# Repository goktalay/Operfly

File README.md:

# OPERFLY

Operfly (Operational Flight), bir uçuş için gereken tüm kartların ve yazılımın tek ekosistem olarak
tasarlandığı kapalı bir sistemdir: uçuş kartları, kartlar arası omurga (Operfly Bus), gömülü yazılım,
kiracılı (çok kurumlu) merkez ve yer istasyonu. Operfly bileşenleri yalnızca birbirleriyle çalışır.

> **Bu depo özeldir (private).** Sır, özel anahtar, parola, canlı veritabanı dökümü veya müşteri verisi
> depoya eklenmez. Üretim çıktıları (gerber, kurulum paketleri) depoda değil, Releases altındadır.

## Ürünler

| Kod | Ad | İşlev | Kaynak |
|---|---|---|---|
| **OPFCOR** | Operfly Core | Uçuş kontrol kartı | `01_DONANIM/CORE/` |
| **OPFPWR** | Operfly Power | Batarya girişi, kart beslemeleri, akım/gerilim ölçümü | `01_DONANIM/POWER/` |
| **OPFVIS** | Operfly Vision | Görüntü işleme kartı (Jetson taşıyıcı, yalnızca Ethernet kamera) | `01_DONANIM/VISION/` |
| **OPFRAD** | Operfly Radio | Geniş bant radyo kartı: video + telemetri (2,4 GHz, 12 km, şifreli, mesh) | `01_DONANIM/RADIO/` |
| **OPFNAV** | Operfly Nav | GNSS kartı (RTK, karıştırma/aldatma tespiti) | `01_DONANIM/NAV/` |
| **OPFTRK** | Operfly Tracker | Anten takip birimi (yer tarafındaki yönlü anteni araca çevirir) | `01_DONANIM/TRACKER/` |
| **OPFSHD** | Operfly Shield | Karıştırma önleyici GNSS anteni: hazır 4 kanallı L1 CRPA modülü + arayüz kartı | `01_DONANIM/SHIELD/` |
| **OPFAIR** | Operfly Air | Hava hızı kartı (pitot fark basınç); sabit kanat için | `01_DONANIM/AIR/` |
| **OPFENG** | Operfly Engine | Benzinli motor izleme ve ateşleme kesme | `01_DONANIM/ENGINE/` |
| **OPFHUB** | Operfly Hub | Omurga anahtar kartı: tüm kartlar buna bağlanır (Gigabit anahtar, CAN FD, güç dağıtımı) | `01_DONANIM/HUB/` |
| **OPFBAS** | Operfly Base | RTK baz istasyonu (yer) | `01_DONANIM/BASE/` |
| **OPFGRD** | Operfly Ground Radio | Yer radyosu | `01_DONANIM/YER_RADYO/` |
| **OPFPCA** | Operfly PC adaptörü | Operfly Bus konnektörü ↔ USB Type-C aktif adaptör | `01_DONANIM/PC_ADAPTOR/` |
| **OPFCEL** | Operfly Cell | 5G kartı: telemetri ve görüntü için hücresel bağlantı | `01_DONANIM/CELL/` |
| **OPFR10 / OPFR30 / OPFR1H** | Operfly Range 10 / 30 / 100 | Mesafe sensörleri: 10 m, 30 m, 100 m | `01_DONANIM/RANGE_10/`, `RANGE_30/`, `RANGE_100/` |
| **OPFRCV** | Operfly RX | Araç tarafı kumanda alıcısı (12 kanal) | `01_DONANIM/RX/` |
| **OPFK12** | Operfly Pilot 12 | Kumanda: yalnızca 12 kanal | `01_DONANIM/KUMANDA_12/` |
| **OPFKTL** | Operfly Pilot T | Kumanda: 12 kanal + telemetri | `01_DONANIM/KUMANDA_T/` |
| **OPFKPR** | Operfly Pilot Pro | Kumanda: 10 inç ekran, yer istasyonu ve video (Jetson) | `01_DONANIM/KUMANDA_PRO/` |
| — | Ortak kart | Kumanda giriş kartı | `01_DONANIM/KUMANDA_GIRIS/` |
| **OPFKMD** | Kumanda yazılımı | Kumandalardaki gömülü yazılım | `02_GOMULU/KUMANDA/` |
| **OPFFLT** | Uçuş yazılımı | Operfly Core üzerinde çalışan otopilot | `02_GOMULU/UCUS/` |
| **OPFNOD** | Düğüm yazılımı | Çevre kartlarındaki Operfly Bus düğümü | `02_GOMULU/DUGUM/` |
| **OPFSEC** | Radyo/kripto yazılımı | Uçtan uca şifreleme, anahtar yönetimi, radyo modülü ayarları | `02_GOMULU/RADYO/` |
| **OPFMRK** | Merkez | Kiracılı çevrimiçi merkez: kurum, filo, cihaz, lisans, güncelleme | `03_MERKEZ/` |
| **OPFGCS** | Yer istasyonu | Çok araçlı görev, izleme ve sürü kontrolü | `04_YER_ISTASYONU/` |
| **OPFIMG** | Görüntü yazılımı | Operfly Vision üzerinde çalışan görüntü işleme | `05_GORUNTU/` |
| **OPFCMP / OPFADM / OPFWEB** | Paneller | Kurum paneli, yönetim paneli, tanıtım sitesi | `06_PANELLER/` |

Bu ürün kodları dosya, klasör, sürüm notu ve teknik iletişimde değişmeden kullanılır.

## Kapsam dışı (dışarıdan alınır)

Batarya, şarj cihazı, motor ve ESC şimdilik dışarıdan satın alınır. Sistem 2S–12S arasındaki hazır
bataryalarla çalışır; kendi bataryası ve şarj cihazı ertelenmiştir.

## Değişmez kurallar

1. **Kapalı ekosistem.** Operfly kartları ve yazılımı yalnızca kimliği doğrulanmış Operfly bileşenleriyle
   konuşur. Üçüncü taraf yer istasyonu yazılımları bağlanamaz.
2. **Marka temizliği.** Üçüncü taraf otopilot, protokol ve yer istasyonu adları kaynak adlarında, arayüzde,
   derlenmiş çıktıda ve cihazın dışarı verdiği hiçbir metinde geçmez. Bu adlar yalnızca
   `13_DOKUMANTASYON/` altında ve üçüncü taraf kaynak dosyalarının korunması zorunlu lisans başlıklarında
   bulunur. Denetim: `10_ORTAK_ARACLAR/marka_denetle.py`.
3. **Kiracı yalıtımı.** Her kurumun cihazları, anahtarları ve verisi diğer kurumlardan ayrıdır.
4. **Sürü önceliği.** Her bileşen çok araçlı kullanım varsayılarak tasarlanır.

Ayrıntı: `13_DOKUMANTASYON/MIMARI.md`.

## Sahiplik

© 2026 Muhammed Kaderoğlu. Tüm hakları saklıdır. Bu depodaki tasarım dosyaları ve yazılım izinsiz
kopyalanamaz, dağıtılamaz veya kullanılamaz.

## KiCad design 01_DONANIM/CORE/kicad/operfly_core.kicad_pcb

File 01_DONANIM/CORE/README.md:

## Pin haritası (15 Kasım 2026)

- Atamalar: `pin_atamalari.csv` (kaynak dosya). Okunabilir tablo: `PIN_HARITASI.md` (üretilir).
- Doğrulama: `python 10_ORTAK_ARACLAR/kicad/pin_cikar.py <KiCad>/symbols/MCU_ST_STM32H7.kicad_sym STM32H753IIKx out/h753iik.json`
  ardından `python 10_ORTAK_ARACLAR/kicad/pin_dogrula.py out/h753iik.json 01_DONANIM/CORE/pin_atamalari.csv 01_DONANIM/CORE/PIN_HARITASI.md "<başlık>"`.
- Kılıf: UFBGA 176+25, 10 x 10 mm, 0,65 mm adım.

Pin haritasından çıkan tasarım notları:

- İşlemcinin Ethernet arayüzü en çok 100 Mbit destekler (MII/RMII). Core–Hub bağlantısı 100 Mbit olur; PTP zaman damgası korunur.
  Core'daki PHY buna göre 10/100 RMII tipinde seçilecek. Omurganın geri kalanı gigabit kalır.
- Uçuş kaydı için microSD yuvası önerildi (SDMMC1 pinleri ayrıldı); onay bekliyor.
- Üç IMU ayrı SPI hatlarında ve ayrı besleme anahtarlarındadır; bir sensörün arızası diğerlerini etkilemez.
- 12 çıkış üç ayrı zamanlayıcıdadır (4 + 4 + 4); DShot ve PWM grupları buna göre seçilir.

## Mimari kararlar (15 Kasım 2026)

- **Çıkışlar:** 12 çıkışın ilk 8'i IO/failsafe işlemcisinin denetimindedir, son 4'ü doğrudan ana işlemciden çıkar.
  İlk 8 çıkışta ana işlemcinin zamanlayıcı sinyali ile IO işlemcisinin sinyali arasında seçim yapan bir anahtar bulunur;
  seçimi IO işlemcisi yapar. Ana işlemci çalışırken DShot dahil tüm protokoller ondan geçer; ana işlemci durursa
  IO işlemcisi çıkışları devralır ve güvenli değerleri sürer.
- **IO/failsafe işlemcisi omurgaya doğrudan bağlıdır (CAN B).** Kumanda alıcısı (RX) omurgada olduğu için IO işlemcisi,
  ana işlemci durduğunda kumandayı ancak CAN üzerinden alabilir. Bu yüzden CAN FD destekli bir işlemci gerekir;
  öneri düğüm işlemcisiyle aynı aile (STM32G0B1). Önceki STM32F103 önerisi CAN FD desteklemediği için bırakıldı.
- **İkinci Bus portu** yalnızca yedek güç ve CAN taşır; Ethernet ve PPS bağlı değildir.
- Sınır: DShot ile sürülen motorlarda IO işlemcisinin devralması motoru güvenli değere getiremez (ESC protokolü açılışta
  seçilir); bu çıkışlarda failsafe, sinyalin kesilmesiyle ESC'nin kendi davranışına dayanır. Servolar ve PWM ESC'lerde
  devralma tam çalışır.

## KiCad projesi (15 Kasım 2026)

- Proje: `kicad/operfly_core.kicad_pro`. Şematik `kicad/uret.py` ile üretilir; `*.kicad_sch` dosyaları ve kütüphane
  tabloları elle düzenlenmez.
- Üretim ve denetim tek komut: `python 10_ORTAK_ARACLAR/kicad/denetle.py CORE operfly_core` (üretir, güncel biçime çevirir,
  ERC çalıştırır, `out/core.pdf` çıkarır).
- Sayfalar: kök (`operfly_core`), omurga portları (`omurga`), işlemci (`islemci`), güç (`guc`), saat/sıfırlama/ayırma
  kondansatörleri (`islemci_destek`), Ethernet/CAN/USB/microSD/PPS (`haberlesme`), sensörler/bellek/güvenli eleman
  (`sensorler`), IO işlemcisi ve çıkışlar (`io`), gözetim/enerji deposu/Peltier (`gozetim`).
- Durum: şematik tamam; ERC 0 hata, 0 uyarı. Sıradaki iş doğrulama listesi ve kart çizimi.
- Diğer kartlar ortak yardımcıları kullanır: `10_ORTAK_ARACLAR/kicad/kart.py` ve `dugum.py` (düğüm devresi).

## Güç ve işlemci destek kararları (15 Kasım 2026, sahibinin onayı beklenmeden alındı)

Bu kararlar gece çalışmasında, onay sorulmadan alındı. Her biri tek satırla geri alınabilir; değiştirilmesi istenen olursa
`kicad/uret.py` içinde ilgili satır düzeltilip şematik yeniden üretilir.

1. **İki omurga girişi diyotla birleştirilir** (2 x Schottky, 60 V 3 A). Basit ve arıza toleranslı; karşılığı diyot
   başına yaklaşık 0,4 V kayıp. İdeal diyot denetleyicisi (kayıpsız) sonraki revizyon için açık seçenek.
2. **Aşırı gerilim koruması:** girişte 18 V kırpma diyotu (SMBJ18A). Omurga 12 V olduğu için 18 V seçildi.
3. **5 V ve 3,3 V ayrı ayrı 12 V'tan üretilir** (AP63205 ve AP63203, 2 A, sabit çıkışlı). Biri arızalanırsa diğeri
   etkilenmez. Otomotiv sınıfı (Q) sürümleri -40..+125 °C çalışır; standart sürüm +85 °C ile sınırlıdır, bu yüzden
   malzeme listesine Q sürümü yazıldı.
4. **Her IMU'nun kendi 3,3 V regülatörü var** (LP5907, düşük gürültü), işlemci tek tek açıp kapatabilir (SENS1/2/3_EN).
   Varsayılan kapalıdır (aşağı çekme direnci); takılan bir sensör güç kesilerek sıfırlanabilir.
5. **Analog besleme** ferrit üzerinden süzülür; ADC referansı ayrıca 10 ohm + kondansatörle süzülür. Ayrı referans
   entegresi yok (ölçümler besleme izleme amaçlı, yüksek doğruluk gerekmiyor).
6. **Yedek pil yok:** VBAT 3,3 V'a bağlı. Saat bilgisi GNSS ve ağ zaman eşlemesinden gelir.
7. **Kristaller:** ana saat 16 MHz, gerçek zaman saati 32,768 kHz. Yük kondansatörü değerleri kristal parça numarası
   seçilince doğrulanacak.
8. **Açılış:** BOOT0 aşağı çekili (her zaman uygulamadan açılır). Fabrika yüklemesi SWD üzerinden yapılır.
9. **Besleme ölçümleri:** 12 V 11:1, 5 V ve 1. sensör beslemesi 2:1 bölücüyle işlemciye gider (36 V'a kadar güvenli).

Doğrulanacaklar (kart çizimine geçmeden): bobin parça numaraları ve doyma akımları, giriş diyotlarında ısıl hesap,
5 V hattının toplam akımı (IO işlemcisi, sensör regülatörleri, omurga dışı yükler), kristal yük kondansatörleri.

## Haberleşme kararları (15 Kasım 2026, sahibinin onayı beklenmeden alındı)

1. **Ethernet alıcı-vericisi LAN8742A**, 50 MHz osilatörle. Aynı saat hem alıcı-vericiye hem işlemciye gider; zaman
   eşlemesi (PTP) için en temiz düzen budur. Karşılığı: kristal yerine osilatör (biraz daha pahalı).
2. **Ethernet hattında trafo var** (Bourns PT61017PEL). Kartlar arası kabloda standart ve en güvenli yol; kartlar arasında
   toprak döngüsünü keser. Trafosuz (kondansatörlü) bağlantı yer kazandırır ama Hub tarafıyla birlikte kararlaştırılmalı.
3. **CAN alıcı-vericisi TJA1051-3** (CAN FD, 5 Mbit/s), her hatta ayrı. İşlemci pinindeki `CAN_x_STB` sinyali bu parçada
   "sessiz mod" girişidir (bekleme değil): yüksekken kart hattı yalnızca dinler.
4. **CAN sonlandırma dirençleri Core'da dizilmez**, yerleri hazırdır. Sonlandırma Hub'dadır.
5. **USB kartı beslemez.** Servis portu yalnızca veri taşır; kart her zaman omurgadan (12 V) beslenir. USB ile masa
   üstünde beslemek istenirse 5 V hattına güç seçici eklenmesi ve 3,3 V regülatörünün 5 V'tan beslenmesi gerekir
   (açık seçenek; ek parça ve kart alanı ister).
6. **microSD beslemesi anahtarlanmaz**, doğrudan 3,3 V'a bağlıdır. Kart kilitlenirse yeniden başlatma gerekir.
7. **PPS 3,3 V lojik** olarak tanımlandı ve omurga belgesine yazıldı. Core girişi 5 V'a dayanıklıdır.
8. `ETH_PPS_OUT` (işlemcinin ürettiği saniye darbesi) şimdilik yalnızca ölçüm noktasına çıkar.

Doğrulanacaklar: trafo pin sırası ve ayak izi (üretici belgesiyle), Hub tarafının 100 Mbit bağlantıda A/B çiftlerini
kullandığı, CAN hattında kabul edilen en yüksek hız için kablo boyu.

## Sensör ve IO işlemcisi kararları (15 Kasım 2026, sahibinin onayı beklenmeden alındı)

1. **Sensör beslemeleri:** 1. hat IMU 1 + barometre 1 + pusula, 2. hat IMU 2 + barometre 2, 3. hat IMU 3. Bir hat
   kapatıldığında o hattaki sensörlerin bağlı olduğu I2C hattı da kullanılamaz (yalnızca sıfırlama sırasında kapatılır).
2. **Barometre 2: MS5611-01BA03** (ICP-20100 yerine). Dağıtıcı ICP-20100'ü "yeni tasarımlar için önerilmez" olarak
   listeliyor. MS5611 farklı üretici ve farklı ölçüm ilkesi; barometre 1 (BMP390) ile ortak hata riskini azaltır.
3. **Güvenli eleman SE050:** `SE_NRST` hattı elemanın güç anahtarı girişini (ENA) sürer. I2C kullanımında ayrı bir
   sıfırlama girişi olmadığı için sıfırlama, beslemesini kesip vererek yapılır.
4. **FRAM: FM25V10** (1 Mbit, SOIC-8).
5. **IO/failsafe işlemcisi: STM32G0B1CET6** (LQFP-48). Kendi 3,3 V regülatörü, kendi kristali ve CAN B üzerinde kendi
   alıcı-vericisi vardır. Pin atamaları `io_pin_atamalari.csv` içindedir ve KiCad pin verisiyle denetlenmiştir.
6. **Çıkış seçici: 2 x TMUX1574** (analog anahtar). Sayısal seçici yerine analog anahtar seçildi çünkü iki yönlü motor
   protokollerini (telemetrili DShot) geçirir. Seçme girişi aşağı çekilidir: IO işlemcisi çalışmıyorken 1-8. çıkışları ana
   işlemci sürer; IO işlemcisi devralmak istediğinde girişi yükseltir. Anahtarlar 5 V'tan beslenir (iki 3,3 V hattından
   bağımsız).
7. **Çıkış konnektörü (26 kontak):** tek numaralı kontaklar 1-12. çıkış, çift numaralı kontaklar GND, 25. kontak boş.
   Her çıkışta 33 ohm seri direnç var. Çıkışlarda ayrıca ESD koruması yok (sonraki revizyon için açık).
8. **IO işlemcisi yazılım yükleme:** ana işlemci `IO_NRST` ile sıfırlar ve seri hattan yükler. `IO_BOOT0`, IO işlemcisinin
   BOOT0/SWCLK ortak pinine 10 k ile bağlıdır; hata ayıklayıcı takılıyken hata ayıklayıcı baskın gelir.
9. **Durum LED'leri** sıfırda yanar. Kart sürümü dirençleri A revizyonu için yerleştirildi (sürüm 1:1, revizyon 10:1).
10. **Hata ayıklama:** ana işlemci için 2x5 (1,27 mm) SWD konnektörü; konsol ve IO işlemcisi SWD hatları ölçüm noktasında.

### Doğrulanacaklar (kart çizimine geçmeden)

- BMP390 ve SE050 ayak izleri geçici; üretici çizimiyle yapılacak. IMU ayak izlerinde pin sırası bir kez daha bakılacak.
- IST8310 VPP ucu boş bırakıldı; üretici belgesindeki öneriyle karşılaştırılacak.
- ICM-42688-P ayrılmış uçları: 7 ve 11 GND'ye, 2, 3 ve 10 boş.
- TMUX1574: seçme girişinin yönü (0 = A kolu) ve 5 V beslemede 3,3 V lojikle sürülmesi.
- STM32G0B1 fabrika yükleyicisinin PA2/PA3 seri hattını desteklediği (boş işlemcinin ana işlemci üzerinden yüklenmesi).
- TPS3808G01 eşik gerilimi (0,405 V varsayıldı) ve 470 µF 25 V kondansatörün 8x10 mm kılıfta bulunabilirliği.
- Enerji deposunun ilk şarj akımı: Hub port anahtarı yaklaşık 1000 µF yükü açılışta kaldırmalı.

## Gözetim ve Peltier kararları (15 Kasım 2026; sahibi kararı tasarımcıya bıraktı)

1. **Harici watchdog ana işlemciyi sıfırlamaz, IO işlemcisini uyarır.** Ana işlemci darbe göndermeyi keserse
   `FMU_FAULT_N` 200 ms sıfıra iner; IO işlemcisi 1-8. çıkışları devralır ve güvenli değerleri sürer. Gerekçe: uçuşta
   donanımın kendiliğinden sıfırlama yapması, yazılım güncelleme ve hata ayıklama sırasında da tetiklenir ve sıfırlama
   döngüsüne yol açabilir. Ana işlemci takılırsa kendi iç watchdog'u onu sıfırlar; o yeniden başlayana kadar uçağı IO
   işlemcisi tutar.
2. **Watchdog penceresi:** darbe aralığı 10-93 ms arasında olmalı (yazılım 30-50 ms'de bir gönderir); kesinti en geç
   yaklaşık 125 ms içinde algılanır. Watchdog IO işlemcisinin beslemesinden çalışır.
3. **IO işlemcisi ana işlemciyi sıfırlayabilsin diye bir hat ayrıldı** (`IO_FMU_RST`) ama direnci dizilmez. İleride
   istenirse tek direnç takılarak açılır.
4. **Güç kesintisi algılama:** giriş 10,1 V altına inince `PWR_FAIL_N` sıfıra iner; işlemci kritik durumu FRAM'e yazar.
5. **Enerji deposu: 2 x 470 µF.** Kesintiden sonra kartı yaklaşık 10-20 ms taşır (kart tüketimi 2-3 W varsayımıyla
   hesap; ölçülecek). FRAM yazımı için yeterlidir; microSD'deki son birkaç yüz milisaniyelik kayıt kaybolabilir.
   Süper kondansatörlü daha uzun taşıma, kart alanı ve şarj devresi gerektirdiği için seçilmedi.
6. **Peltier sürücüsü: DRV8837**, 5 V'tan, en çok 1 A. Çıkışta bobin ve kondansatör var (anahtarlama gürültüsü pusula
   ve IMU'yu bozmasın diye). Isıl hedef varsayılan 45 °C, yazılımla değişir; sıcaklık IMU'ların kendi sensöründen okunur.
   Peltier modülünün kendisi mekanik tasarımla birlikte seçilecek (en çok 5 V, 1 A).

## Kart çizimi (otomatik)

Sahibinin kararıyla kart **otomatik** çizildi: yerleşim `pcb_yerlesim.py`, yollar dış bir otomatik yol çiziciyle
(`pcb_ciz.py`). Dosya: `kicad/operfly_core.kicad_pcb`; ayarlar `kicad/pcb_ayar.py`.
Yeniden üretmek için: `python 10_ORTAK_ARACLAR/kicad/pcb_ciz.py CORE operfly_core`.

- **Kart:** 125 x 85 mm, 6 katman (iç 1: toprak, iç 4: +3V3; diğer katmanlar sinyal, elemanlar üstte), 264 eleman, tamamı üst yüzde; köşelerde M3 montaj deliği.
- **Kurallar:** yol 0,10 mm, açıklık 0,100 mm, geçiş 0,40/0,20 mm; besleme ağları, ağın en dar ucunu aşmayacak biçimde 0,2-1,0 mm (0,4 mm ve üstünde geçiş 0,8/0,4 mm); bakır-kenar 0,25 mm.
- **Denetim: KART TAMAMLANMADI.** DRC 0 ihlal (-), 3 bağlanmamış uç. Otomatik yol çizici bu kartı bitiremedi;
  kalan bağlantılar elle çizilmeli ya da yerleşim elle düzeltilip yeniden denenmeli.

**Bu bir mühendis çizimi değildir.** Üretimden önce bir kart tasarımcısının bakması gereken noktalar:

- Eksik kalan üç bağlantı: +3V3, +3V3_S2, IMU2_MOSI. Üç ayrı yerleşim denendi (ilki 120 turda 4 eksik, ikincisi 10 eksik, bu üçüncüsü 60 turda 3 eksik; `OPERFLY_YOL_CIZICI` 1.9.0, `OPERFLY_YOL_TUR=60`, deneme başına yaklaşık 3 saat). Otomatik yol çizici bu kartı bitiremiyor; kalanlar elle çizilmeli.
- İşlemci 0,65 mm adımlı BGA olduğu için ince kural kullanıldı (yol ve açıklık 0,10 mm, geçiş 0,4/0,2 mm): bu, standart değil ileri sınıf üretim ister; üreticinin yetenekleriyle karşılaştırılmalı.
- Üç IMU'nun mekanik yalıtımı, ısıtıcı/Peltier bölgesi ve IMU'ların ısı kaynaklarından uzaklığı gözetilmedi; uçuş denetçisinde ölçüm kalitesi doğrudan buna bağlıdır.
- İşlemci çekirdek beslemesi ve BGA altı ayırma kondansatörleri üretici önerisine göre yerleştirilmedi; Ethernet (RMII), USB ve microSD hatları eşit uzunlukta çizilmedi.
- Servo/motor çıkışları (12 kanal) ve yedek işlemci yolu için gürültü ve arıza yalıtımı gözetilmedi.
- Anahtarlamalı regülatörlerin (bobin, diyot, giriş/çıkış kondansatörleri) akım döngüleri küçük tutulmadı; gürültü ve verim ölçülmeli.
- Kristal ve osilatör hatları en kısa yoldan çizilmedi; altlarından başka sinyal geçip geçmediğine bakılmalı.
- Fark çiftleri (CAN, USB, Ethernet) çift olarak, eşit uzunlukta ve empedans denetimli çizilmedi.
- Güç elemanlarının soğutma bakırı ve ısıl geçişleri ayrıca hesaplanmadı.
- Eleman adları üretim katmanında bırakıldı; kart üstünde yazı (serigrafi) yok.
- Kasa, konnektör yerleri ve montaj delikleri mekanik tasarımla eşleştirilmedi.
- Üretim dosyaları (Gerber, delik, dizgi) henüz çıkarılmadı.

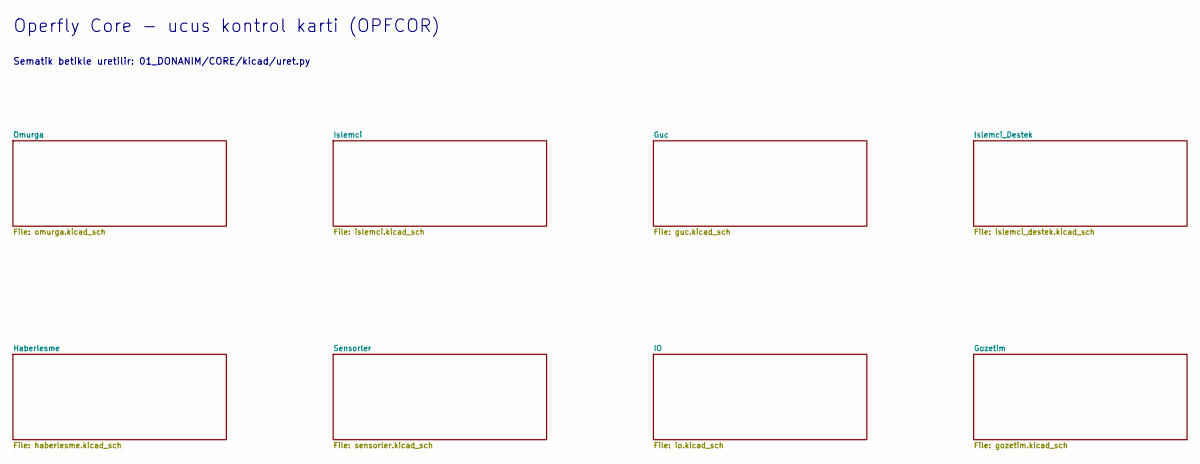
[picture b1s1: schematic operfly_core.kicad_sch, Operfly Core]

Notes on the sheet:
Operfly Core - ucus kontrol karti (OPFCOR)
Sematik betikle uretilir: 01_DONANIM/CORE/kicad/uret.py

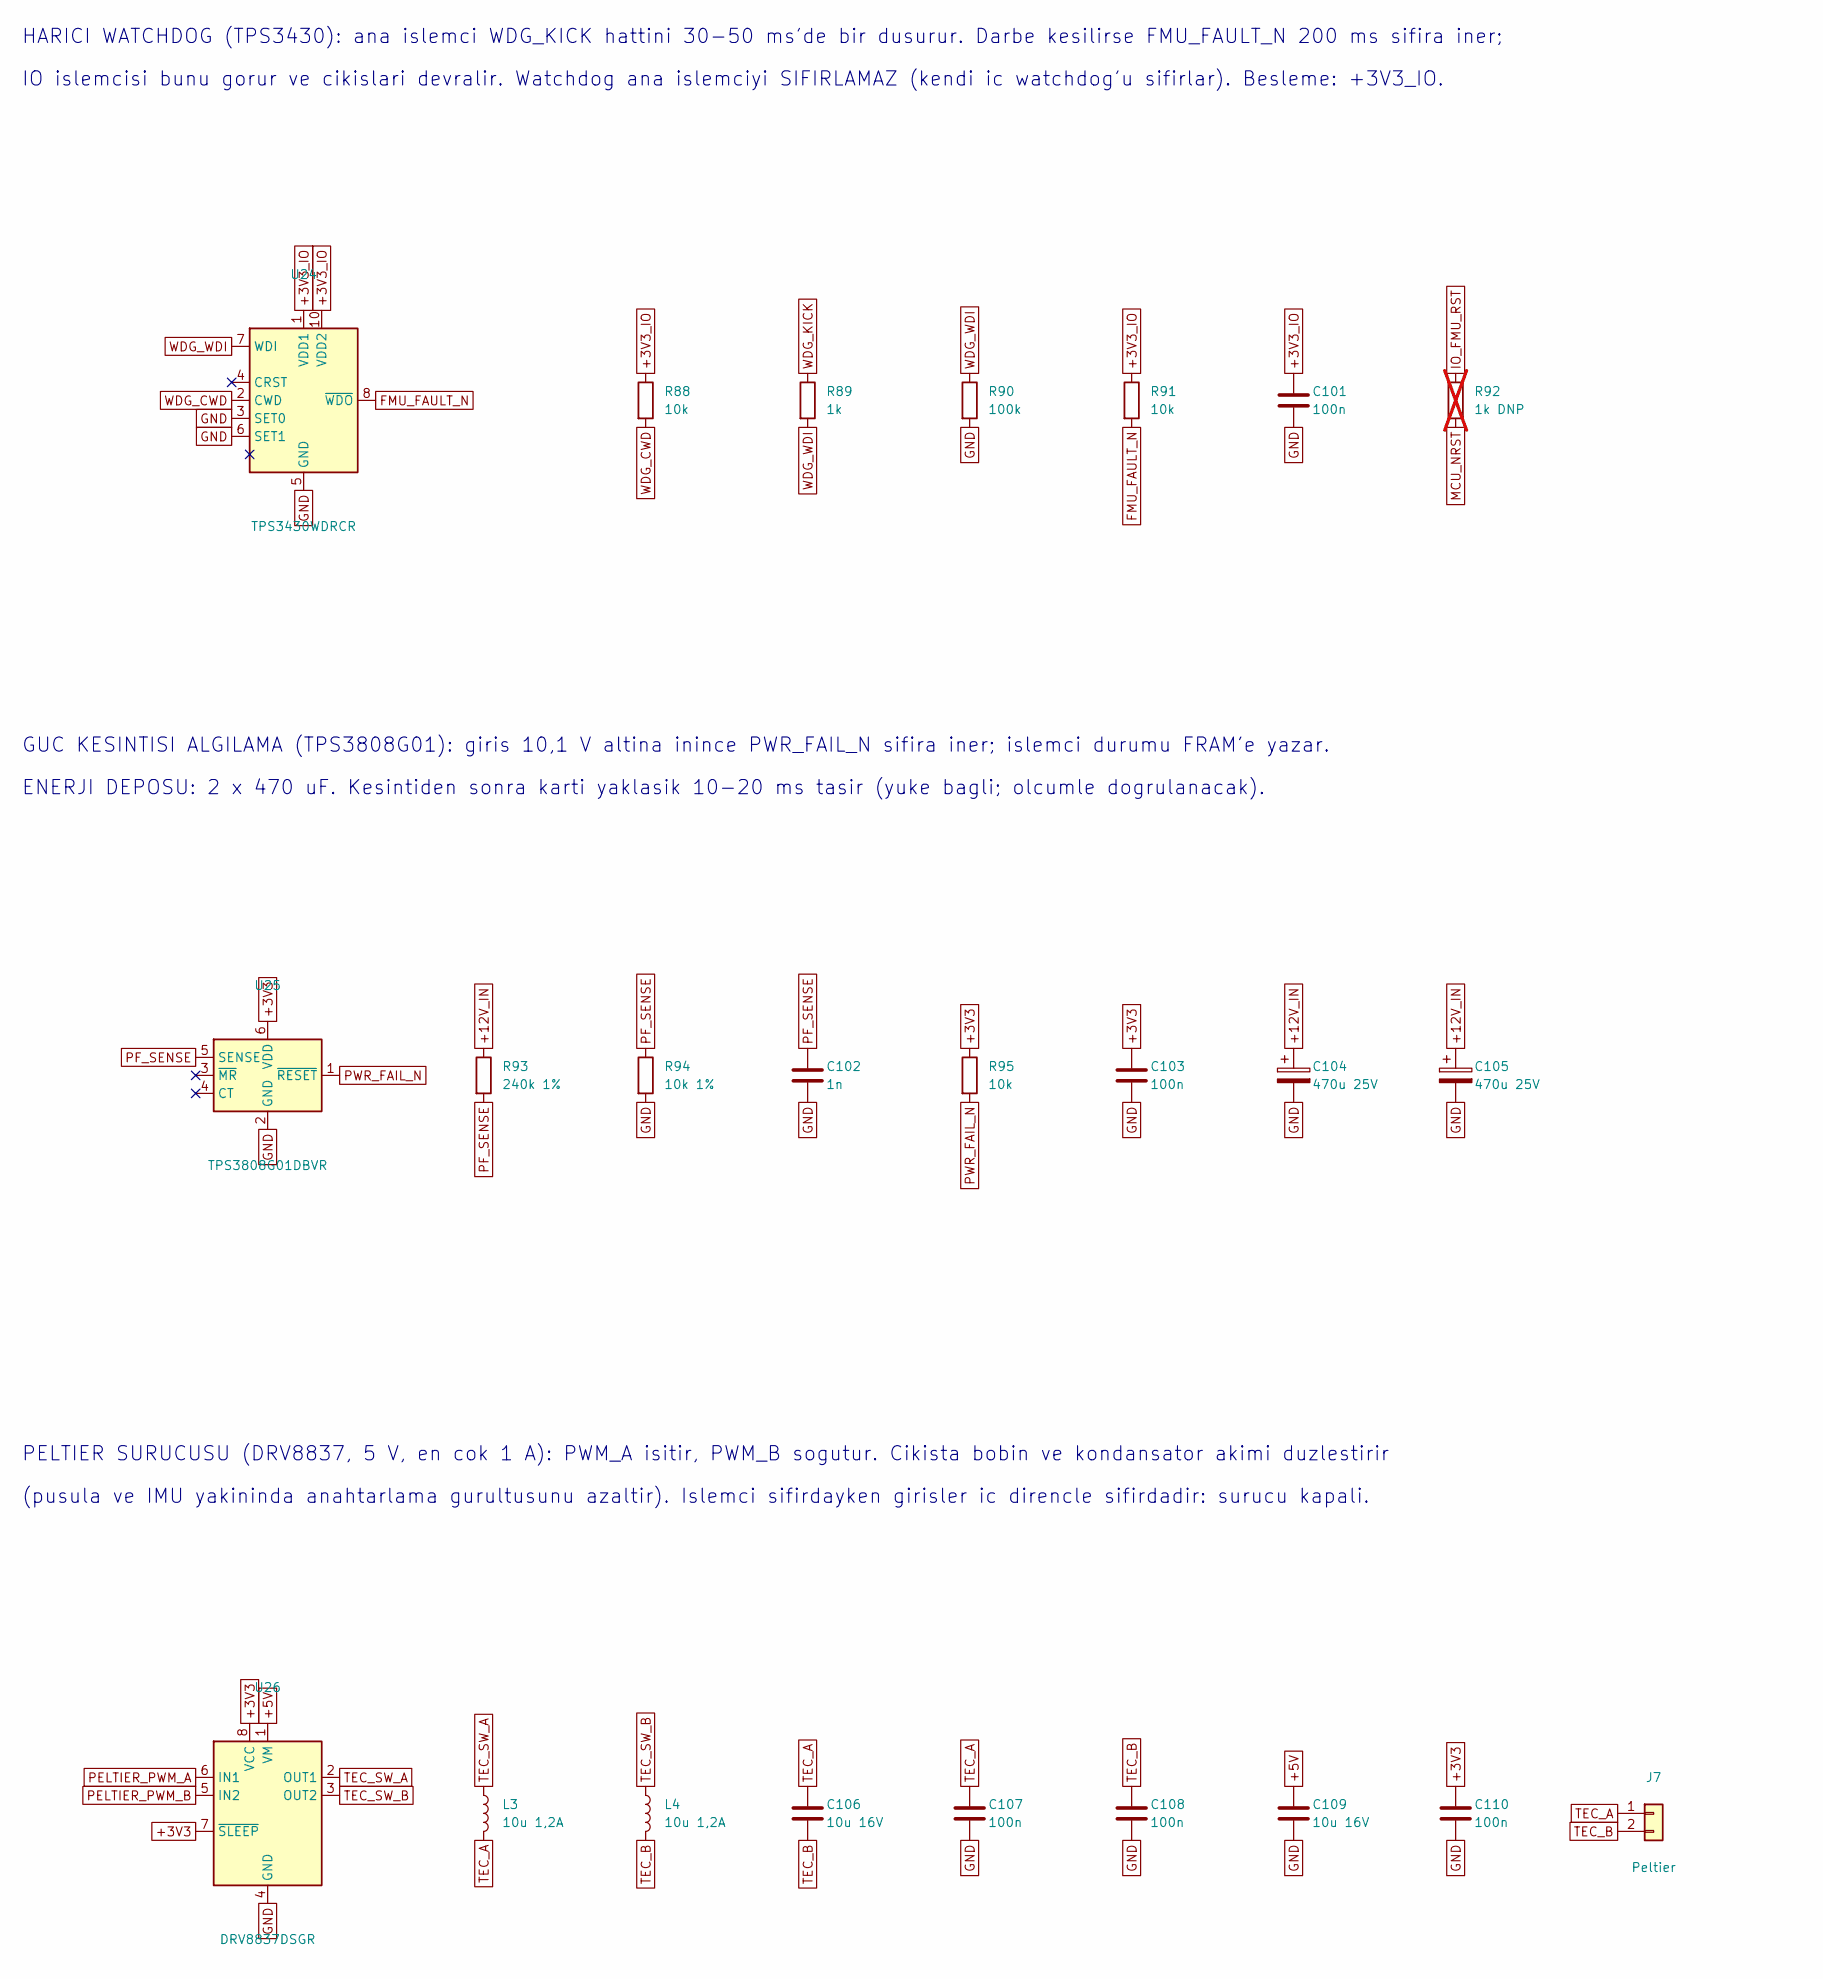
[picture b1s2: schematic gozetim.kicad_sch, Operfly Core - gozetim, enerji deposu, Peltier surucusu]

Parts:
C101, C103, C107, C108, C110: 100n; C_0402_1005Metric
C102: 1n; C_0402_1005Metric
C104, C105: 470u 25V; CP_Elec_8x10
C106, C109: 10u 16V; C_0805_2012Metric
J7: Peltier; JST_SH_SM02B-SRSS-TB_1x02-1MP_P1.00mm_Horizontal
L3, L4: 10u 1,2A; L_Taiyo-Yuden_NR-40xx
R88, R91, R95: 10k; R_0402_1005Metric
R89: 1k; R_0402_1005Metric
R90: 100k; R_0402_1005Metric
R92: 1k DNP; R_0402_1005Metric; not fitted
R93: 240k 1%; R_0402_1005Metric
R94: 10k 1%; R_0402_1005Metric
U24: TPS3430WDRCR; VSON-10-1EP_3x3mm_P0.5mm_EP1.2x2mm
U25: TPS3808G01DBVR; SOT-23-6
U26: DRV8837DSGR; Texas_DSG0008A_WSON-8-1EP_2x2mm_P0.5mm_EP0.9x1.6mm

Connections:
+3V3: C103.1, C110.1, R95.1, U25.6 (VDD), U26.7 (~SLEEP), U26.8 (VCC); also elsewhere on the board
+3V3_IO: C101.1, R88.1, R91.1, U24.1 (VDD1), U24.10 (VDD2); also elsewhere on the board
+5V: C109.1, U26.1 (VM); also elsewhere on the board
+12V_IN: C104.1, C105.1, R93.1; also elsewhere on the board
FMU_FAULT_N: R91.2, U24.8 (~WDO); also elsewhere on the board
GND: C101.2, C102.2, C103.2, C104.2, C105.2, C107.2, C108.2, C109.2, C110.2, R90.2, R94.2, U24.3 (SET0), U24.5 (GND), U24.6 (SET1), U24.11 (GND), U25.2 (GND), U26.4 (GND), U26.9 (GND); also elsewhere on the board
IO_FMU_RST: R92.1; also elsewhere on the board
MCU_NRST: R92.2; also elsewhere on the board
PELTIER_PWM_A: U26.6 (IN1); also elsewhere on the board
PELTIER_PWM_B: U26.5 (IN2); also elsewhere on the board
PF_SENSE: C102.1, R93.2, R94.1, U25.5 (SENSE)
PWR_FAIL_N: R95.2, U25.1 (~RESET); also elsewhere on the board
TEC_A: C106.1, C107.1, J7.1, L3.2
TEC_B: C106.2, C108.1, J7.2, L4.2
TEC_SW_A: L3.1, U26.2 (OUT1)
TEC_SW_B: L4.1, U26.3 (OUT2)
WDG_CWD: R88.2, U24.2 (CWD)
WDG_KICK: R89.1; also elsewhere on the board
WDG_WDI: R89.2, R90.1, U24.7 (WDI)

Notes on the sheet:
(pusula ve IMU yakininda anahtarlama gurultusunu azaltir). Islemci sifirdayken girisler ic direncle sifirdadir: surucu kapali.
HARICI WATCHDOG (TPS3430): ana islemci WDG_KICK hattini 30-50 ms'de bir dusurur. Darbe kesilirse FMU_FAULT_N 200 ms sifira iner;
IO islemcisi bunu gorur ve cikislari devralir. Watchdog ana islemciyi SIFIRLAMAZ (kendi ic watchdog'u sifirlar). Besleme: +3V3_IO.
PELTIER SURUCUSU (DRV8837, 5 V, en cok 1 A): PWM_A isitir, PWM_B sogutur. Cikista bobin ve kondansator akimi duzlestirir
ENERJI DEPOSU: 2 x 470 uF. Kesintiden sonra karti yaklasik 10-20 ms tasir (yuke bagli; olcumle dogrulanacak).
GUC KESINTISI ALGILAMA (TPS3808G01): giris 10,1 V altina inince PWR_FAIL_N sifira iner; islemci durumu FRAM'e yazar.

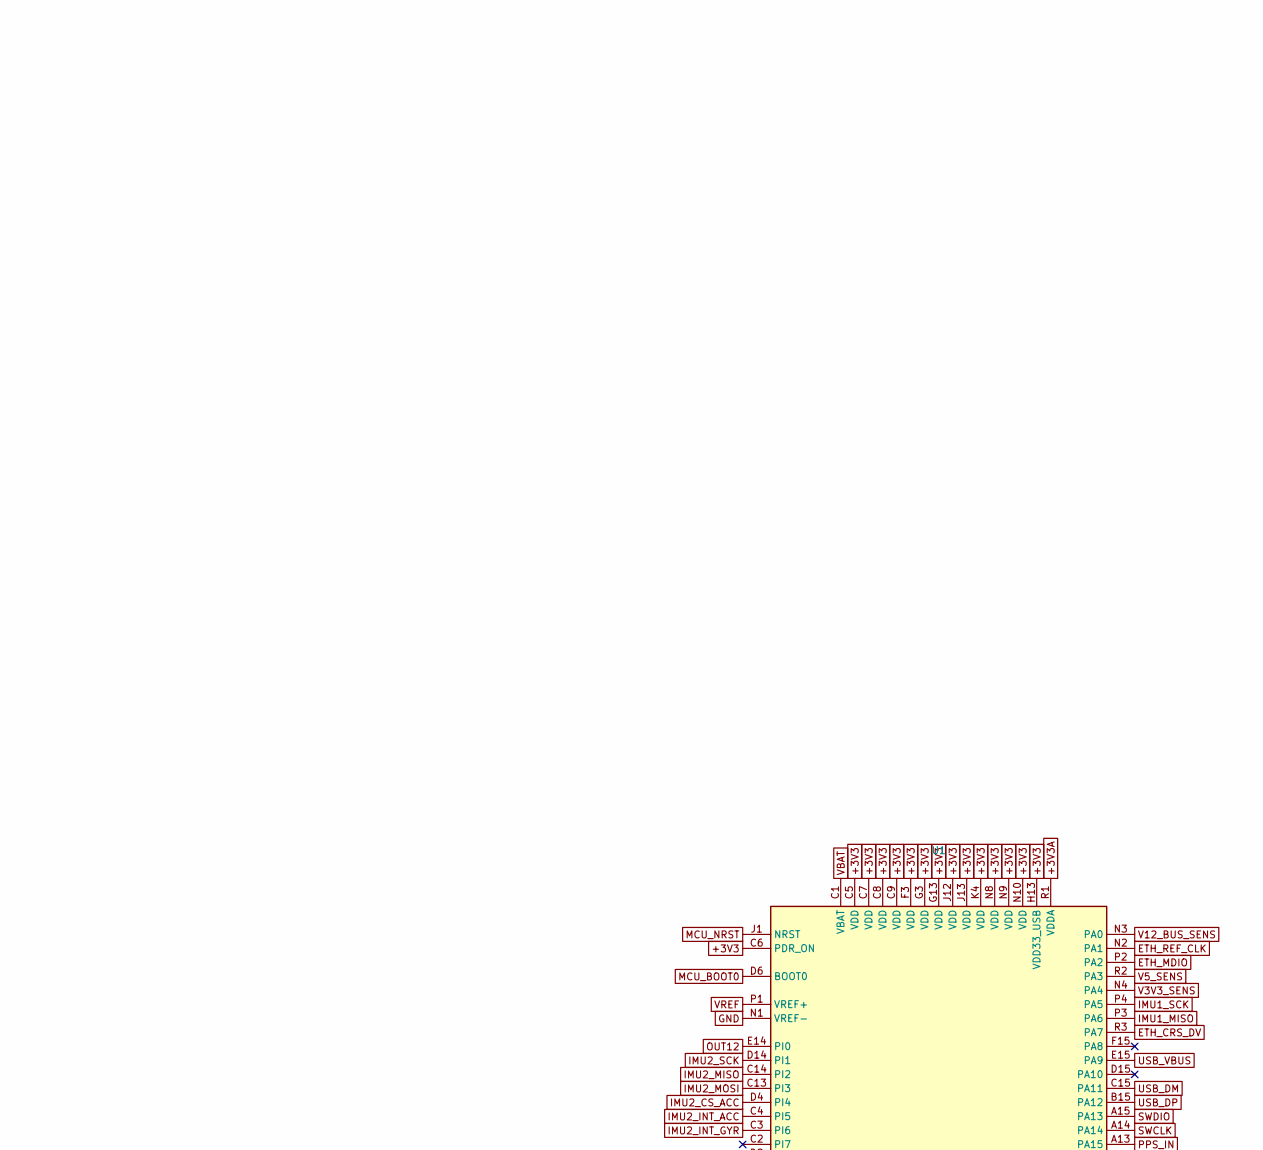
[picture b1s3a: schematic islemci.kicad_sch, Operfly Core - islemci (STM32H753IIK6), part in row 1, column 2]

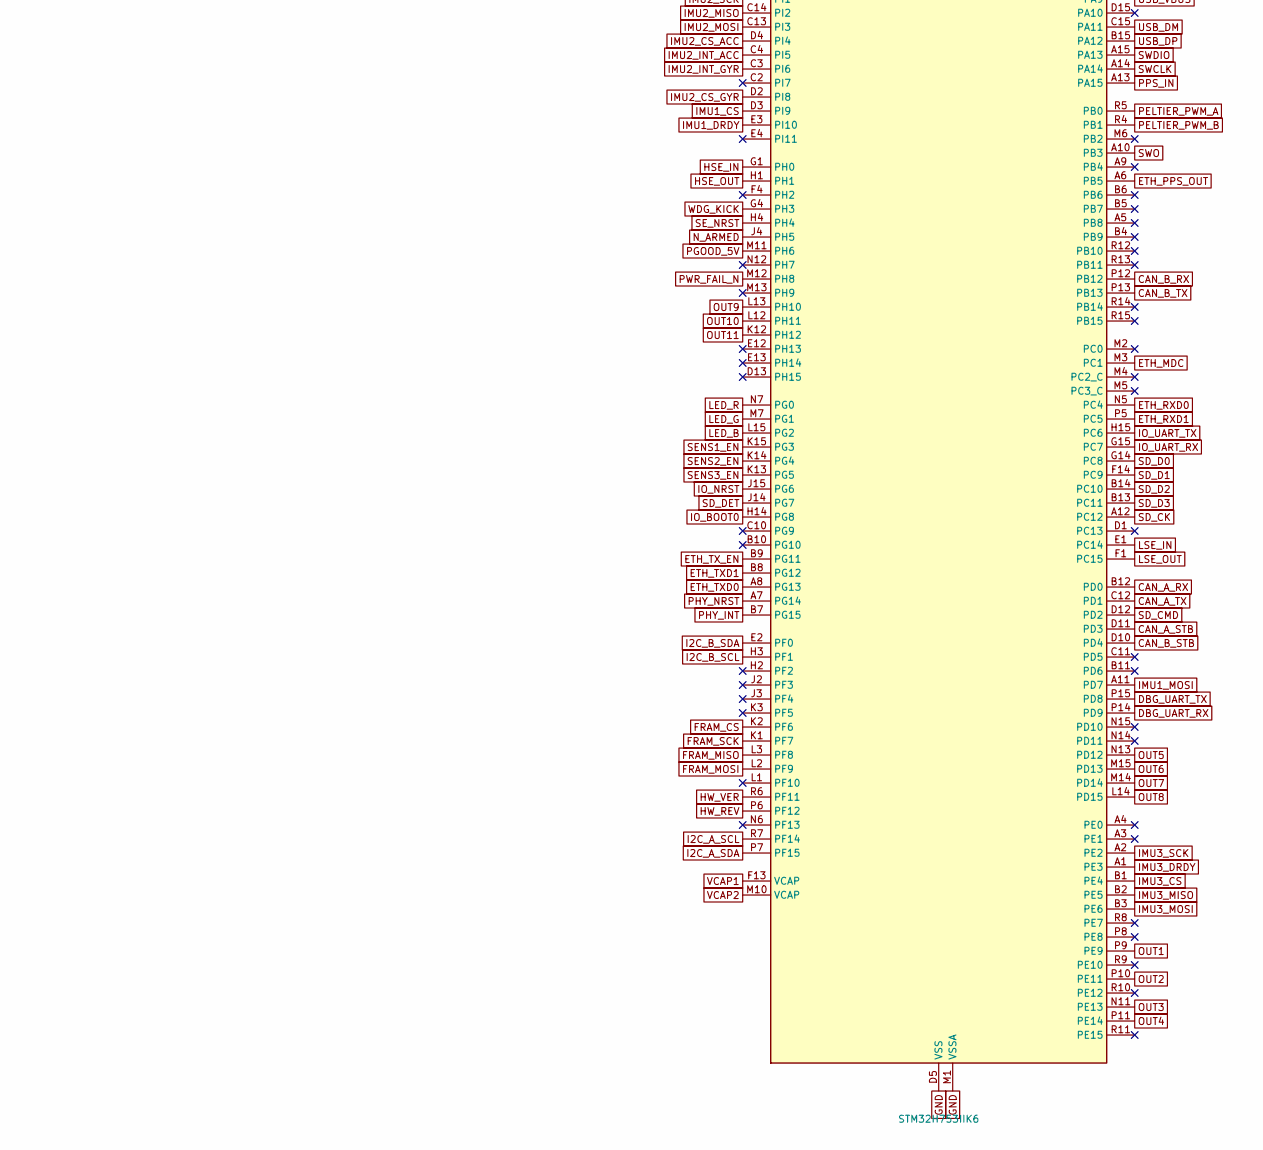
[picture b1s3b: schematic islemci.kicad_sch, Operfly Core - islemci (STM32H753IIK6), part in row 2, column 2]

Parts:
U1: STM32H753IIK6; UFBGA-201_10x10mm_Layout15x15_P0.65mm

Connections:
+3V3: U1.C5 (VDD), U1.C6 (PDR_ON), U1.C7 (VDD), U1.C8 (VDD), U1.C9 (VDD), U1.F3 (VDD), U1.G3 (VDD), U1.G13 (VDD), U1.H13 (VDD33_USB), U1.J12 (VDD), U1.J13 (VDD), U1.K4 (VDD), U1.N8 (VDD), U1.N9 (VDD), U1.N10 (VDD); also elsewhere on the board
+3V3A: U1.R1 (VDDA); also elsewhere on the board
CAN_A_RX: U1.B12 (PD0); also elsewhere on the board
CAN_A_STB: U1.D11 (PD3); also elsewhere on the board
CAN_A_TX: U1.C12 (PD1); also elsewhere on the board
CAN_B_RX: U1.P12 (PB12); also elsewhere on the board
CAN_B_STB: U1.D10 (PD4); also elsewhere on the board
CAN_B_TX: U1.P13 (PB13); also elsewhere on the board
DBG_UART_RX: U1.P14 (PD9); also elsewhere on the board
DBG_UART_TX: U1.P15 (PD8); also elsewhere on the board
ETH_CRS_DV: U1.R3 (PA7); also elsewhere on the board
ETH_MDC: U1.M3 (PC1); also elsewhere on the board
ETH_MDIO: U1.P2 (PA2); also elsewhere on the board
ETH_PPS_OUT: U1.A6 (PB5); also elsewhere on the board
ETH_REF_CLK: U1.N2 (PA1); also elsewhere on the board
ETH_RXD0: U1.N5 (PC4); also elsewhere on the board
ETH_RXD1: U1.P5 (PC5); also elsewhere on the board
ETH_TXD0: U1.A8 (PG13); also elsewhere on the board
ETH_TXD1: U1.B8 (PG12); also elsewhere on the board
ETH_TX_EN: U1.B9 (PG11); also elsewhere on the board
FRAM_CS: U1.K2 (PF6); also elsewhere on the board
FRAM_MISO: U1.L3 (PF8); also elsewhere on the board
FRAM_MOSI: U1.L2 (PF9); also elsewhere on the board
FRAM_SCK: U1.K1 (PF7); also elsewhere on the board
GND: U1.D5 (VSS), U1.D7 (VSS), U1.D8 (VSS), U1.D9 (VSS), U1.F2 (VSS), U1.F6 (VSS), U1.F7 (VSS), U1.F8 (VSS), U1.F9 (VSS), U1.F10 (VSS), U1.F12 (VSS), U1.G2 (VSS), U1.G6 (VSS), U1.G7 (VSS), U1.G8 (VSS), U1.G9 (VSS), U1.G10 (VSS), U1.G12 (VSS), U1.H6 (VSS), U1.H7 (VSS), U1.H8 (VSS), U1.H9 (VSS), U1.H10 (VSS), U1.H12 (VSS), U1.J6 (VSS), U1.J7 (VSS), U1.J8 (VSS), U1.J9 (VSS), U1.J10 (VSS), U1.K6 (VSS), U1.K7 (VSS), U1.K8 (VSS), U1.K9 (VSS), U1.K10 (VSS), U1.L4 (VSS), U1.M1 (VSSA), U1.M8 (VSS), U1.M9 (VSS), U1.N1 (VREF-); also elsewhere on the board
HSE_IN: U1.G1 (PH0); also elsewhere on the board
HSE_OUT: U1.H1; also elsewhere on the board
HW_REV: U1.P6 (PF12); also elsewhere on the board
HW_VER: U1.R6 (PF11); also elsewhere on the board
I2C_A_SCL: U1.R7 (PF14); also elsewhere on the board
I2C_A_SDA: U1.P7 (PF15); also elsewhere on the board
I2C_B_SCL: U1.H3 (PF1); also elsewhere on the board
I2C_B_SDA: U1.E2 (PF0); also elsewhere on the board
IMU1_CS: U1.D3 (PI9); also elsewhere on the board
IMU1_DRDY: U1.E3 (PI10); also elsewhere on the board
IMU1_MISO: U1.P3 (PA6); also elsewhere on the board
IMU1_MOSI: U1.A11 (PD7); also elsewhere on the board
IMU1_SCK: U1.P4 (PA5); also elsewhere on the board
IMU2_CS_ACC: U1.D4 (PI4); also elsewhere on the board
IMU2_CS_GYR: U1.D2 (PI8); also elsewhere on the board
IMU2_INT_ACC: U1.C4 (PI5); also elsewhere on the board
IMU2_INT_GYR: U1.C3 (PI6); also elsewhere on the board
IMU2_MISO: U1.C14 (PI2); also elsewhere on the board
IMU2_MOSI: U1.C13 (PI3); also elsewhere on the board
IMU2_SCK: U1.D14 (PI1); also elsewhere on the board
IMU3_CS: U1.B1 (PE4); also elsewhere on the board
IMU3_DRDY: U1.A1 (PE3); also elsewhere on the board
IMU3_MISO: U1.B2 (PE5); also elsewhere on the board
IMU3_MOSI: U1.B3 (PE6); also elsewhere on the board
IMU3_SCK: U1.A2 (PE2); also elsewhere on the board
IO_BOOT0: U1.H14 (PG8); also elsewhere on the board
IO_NRST: U1.J15 (PG6); also elsewhere on the board
IO_UART_RX: U1.G15 (PC7); also elsewhere on the board
IO_UART_TX: U1.H15 (PC6); also elsewhere on the board
LED_B: U1.L15 (PG2); also elsewhere on the board
LED_G: U1.M7 (PG1); also elsewhere on the board
LED_R: U1.N7 (PG0); also elsewhere on the board
LSE_IN: U1.E1 (PC14); also elsewhere on the board
LSE_OUT: U1.F1 (PC15); also elsewhere on the board
MCU_BOOT0: U1.D6 (BOOT0); also elsewhere on the board
MCU_NRST: U1.J1 (NRST); also elsewhere on the board
N_ARMED: U1.J4 (PH5); also elsewhere on the board
OUT1: U1.P9 (PE9); also elsewhere on the board
OUT2: U1.P10 (PE11); also elsewhere on the board
OUT3: U1.N11 (PE13); also elsewhere on the board
OUT4: U1.P11 (PE14); also elsewhere on the board
OUT5: U1.N13 (PD12); also elsewhere on the board
OUT6: U1.M15 (PD13); also elsewhere on the board
OUT7: U1.M14 (PD14); also elsewhere on the board
OUT8: U1.L14 (PD15); also elsewhere on the board
OUT9: U1.L13 (PH10); also elsewhere on the board
OUT10: U1.L12 (PH11); also elsewhere on the board
OUT11: U1.K12 (PH12); also elsewhere on the board
OUT12: U1.E14 (PI0); also elsewhere on the board
PELTIER_PWM_A: U1.R5 (PB0); also elsewhere on the board
PELTIER_PWM_B: U1.R4 (PB1); also elsewhere on the board
PGOOD_5V: U1.M11 (PH6); also elsewhere on the board
PHY_INT: U1.B7 (PG15); also elsewhere on the board
PHY_NRST: U1.A7 (PG14); also elsewhere on the board
PPS_IN: U1.A13 (PA15); also elsewhere on the board
PWR_FAIL_N: U1.M12 (PH8); also elsewhere on the board
SD_CK: U1.A12 (PC12); also elsewhere on the board
SD_CMD: U1.D12 (PD2); also elsewhere on the board
SD_D0: U1.G14 (PC8); also elsewhere on the board
SD_D1: U1.F14 (PC9); also elsewhere on the board
SD_D2: U1.B14 (PC10); also elsewhere on the board
SD_D3: U1.B13 (PC11); also elsewhere on the board
SD_DET: U1.J14 (PG7); also elsewhere on the board
SENS1_EN: U1.K15 (PG3); also elsewhere on the board
SENS2_EN: U1.K14 (PG4); also elsewhere on the board
SENS3_EN: U1.K13 (PG5); also elsewhere on the board
SE_NRST: U1.H4; also elsewhere on the board
SWCLK: U1.A14; also elsewhere on the board
SWDIO: U1.A15 (PA13); also elsewhere on the board
SWO: U1.A10 (PB3); also elsewhere on the board
USB_DM: U1.C15 (PA11); also elsewhere on the board
USB_DP: U1.B15 (PA12); also elsewhere on the board
USB_VBUS: U1.E15 (PA9); also elsewhere on the board
V3V3_SENS: U1.N4 (PA4); also elsewhere on the board
V5_SENS: U1.R2 (PA3); also elsewhere on the board
V12_BUS_SENS: U1.N3 (PA0); also elsewhere on the board
VBAT: U1.C1 (VBAT); also elsewhere on the board
VCAP1: U1.F13 (VCAP); also elsewhere on the board
VCAP2: U1.M10 (VCAP); also elsewhere on the board
VREF: U1.P1 (VREF+); also elsewhere on the board
WDG_KICK: U1.G4 (PH3); also elsewhere on the board

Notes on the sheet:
Pin atamalari: 01_DONANIM/CORE/pin_atamalari.csv. Etiketsiz pinler bostur.

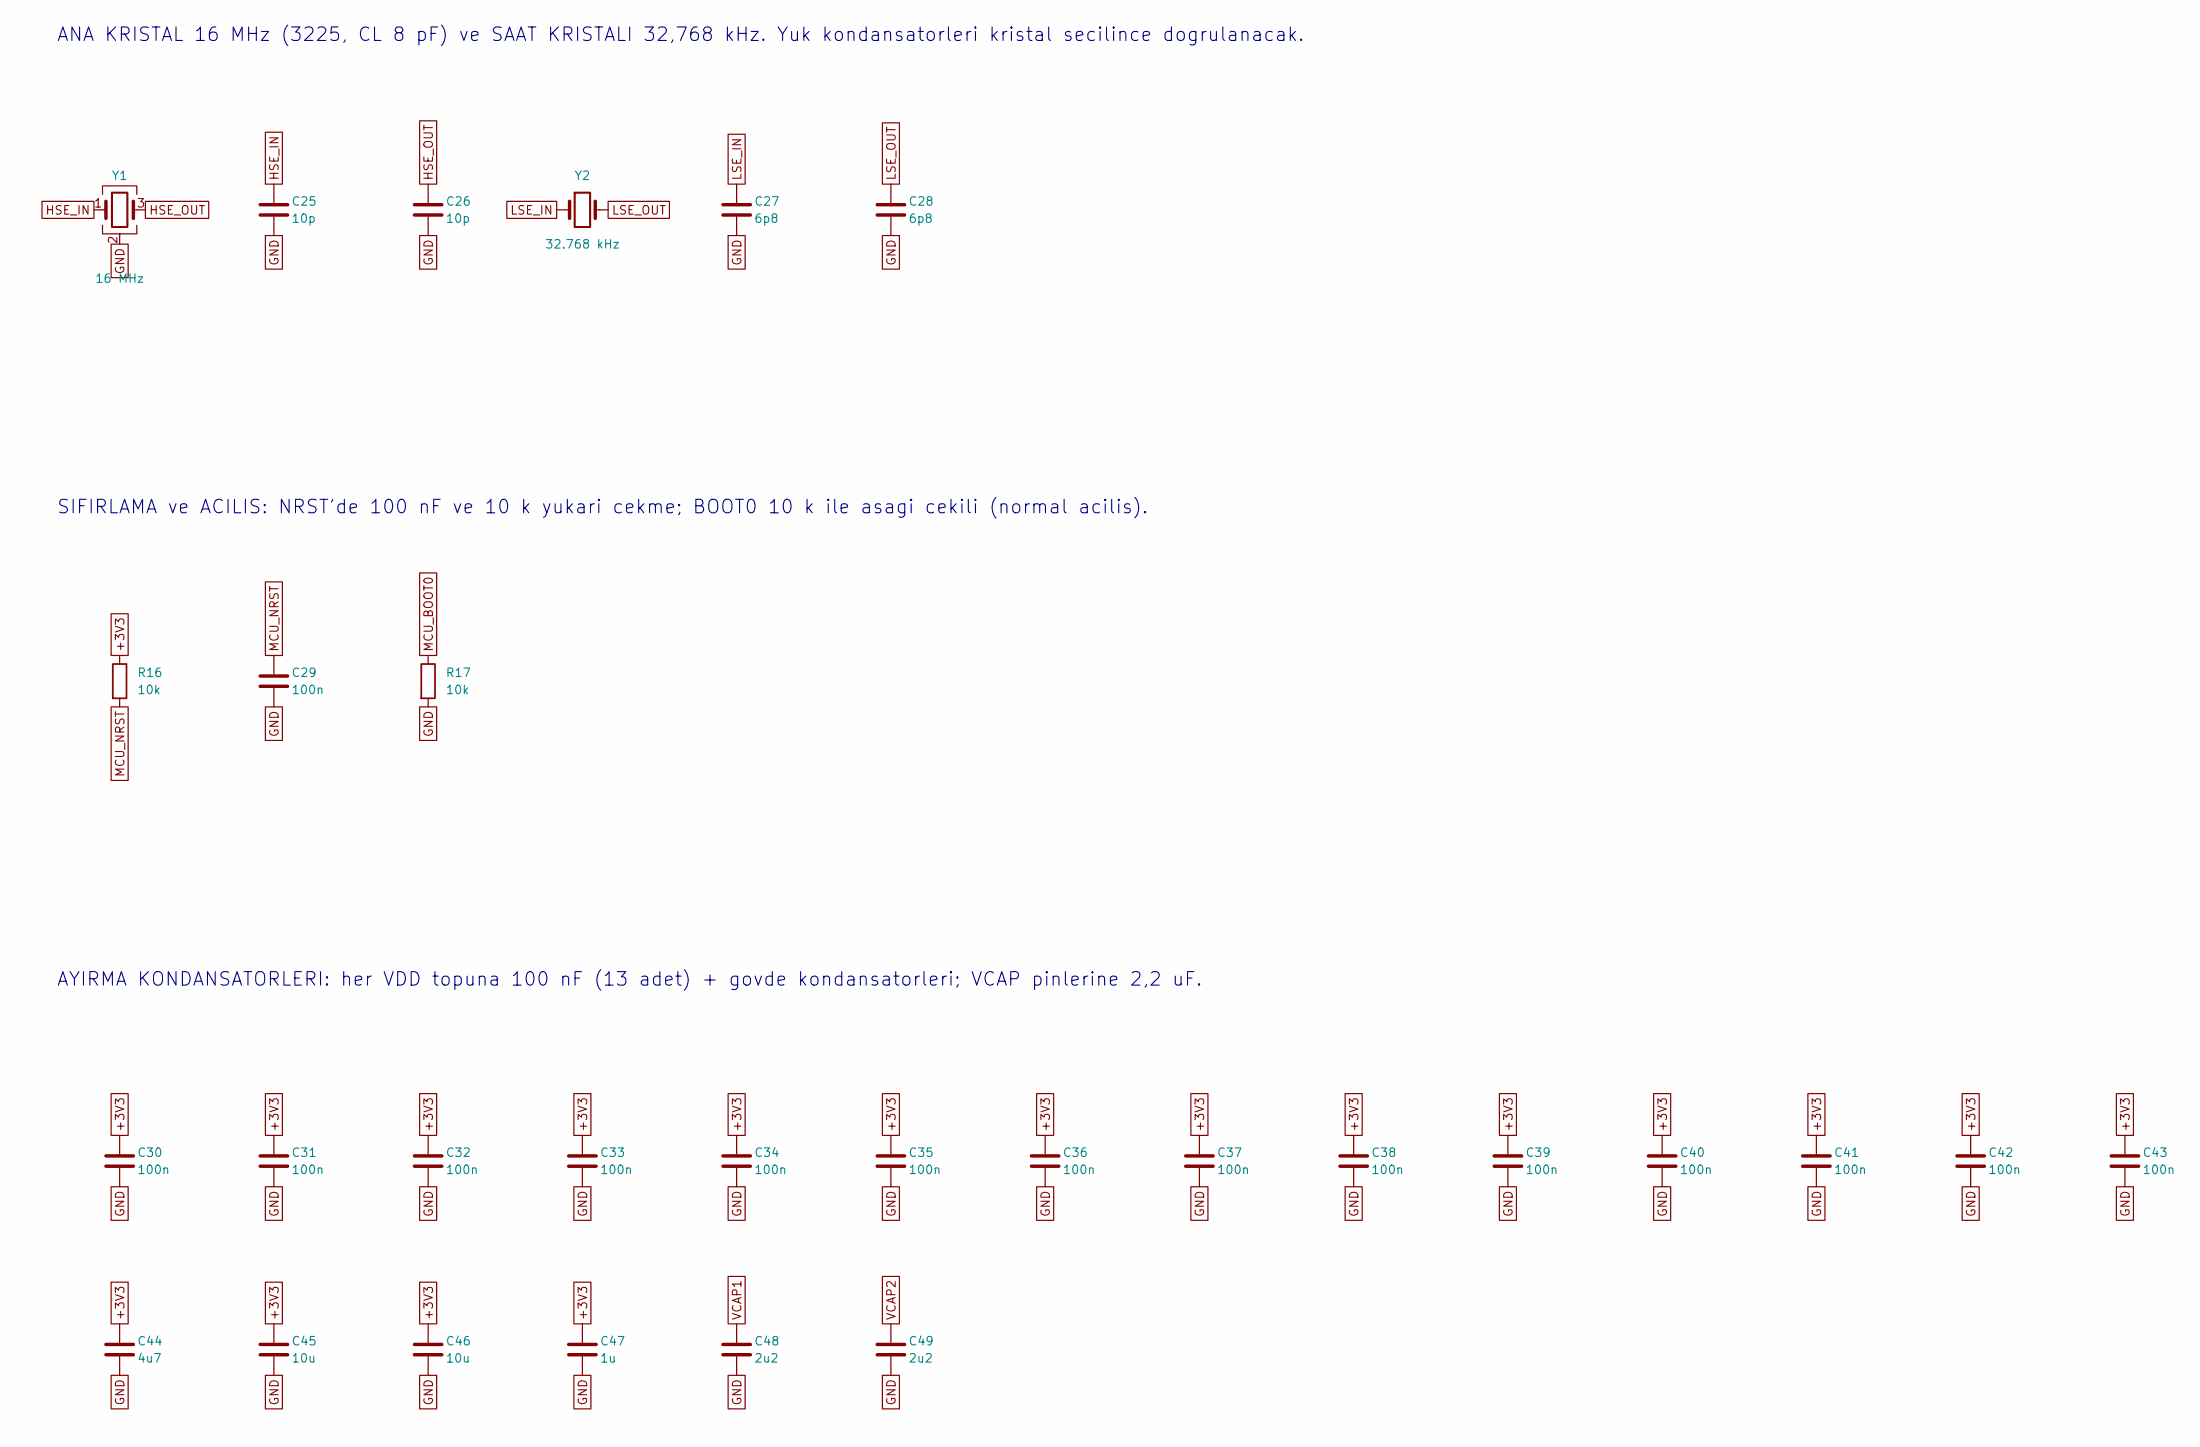
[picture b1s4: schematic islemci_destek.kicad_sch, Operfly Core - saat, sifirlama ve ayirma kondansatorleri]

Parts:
C25, C26: 10p; C_0402_1005Metric
C27, C28: 6p8; C_0402_1005Metric
C29, C30, C31, C32, C33, C34, C35, C36, C37, C38, C39, C40, C41, C42, C43: 100n; C_0402_1005Metric
C44: 4u7; C_0603_1608Metric
C45, C46: 10u; C_0805_2012Metric
C47: 1u; C_0402_1005Metric
C48, C49: 2u2; C_0603_1608Metric
R16, R17: 10k; R_0402_1005Metric
Y1: 16 MHz; Crystal_SMD_3225-4Pin_3.2x2.5mm
Y2: 32.768 kHz; Crystal_SMD_3215-2Pin_3.2x1.5mm

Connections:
+3V3: C30.1, C31.1, C32.1, C33.1, C34.1, C35.1, C36.1, C37.1, C38.1, C39.1, C40.1, C41.1, C42.1, C43.1, C44.1, C45.1, C46.1, C47.1, R16.1; also elsewhere on the board
GND: C25.2, C26.2, C27.2, C28.2, C29.2, C30.2, C31.2, C32.2, C33.2, C34.2, C35.2, C36.2, C37.2, C38.2, C39.2, C40.2, C41.2, C42.2, C43.2, C44.2, C45.2, C46.2, C47.2, C48.2, C49.2, R17.2, Y1.2 (G), Y1.4 (G); also elsewhere on the board
HSE_IN: C25.1, Y1.1; also elsewhere on the board
HSE_OUT: C26.1, Y1.3; also elsewhere on the board
LSE_IN: C27.1, Y2.1; also elsewhere on the board
LSE_OUT: C28.1, Y2.2; also elsewhere on the board
MCU_BOOT0: R17.1; also elsewhere on the board
MCU_NRST: C29.1, R16.2; also elsewhere on the board
VCAP1: C48.1; also elsewhere on the board
VCAP2: C49.1; also elsewhere on the board

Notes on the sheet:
ANA KRISTAL 16 MHz (3225, CL 8 pF) ve SAAT KRISTALI 32,768 kHz. Yuk kondansatorleri kristal secilince dogrulanacak.
AYIRMA KONDANSATORLERI: her VDD topuna 100 nF (13 adet) + govde kondansatorleri; VCAP pinlerine 2,2 uF.
SIFIRLAMA ve ACILIS: NRST'de 100 nF ve 10 k yukari cekme; BOOT0 10 k ile asagi cekili (normal acilis).
